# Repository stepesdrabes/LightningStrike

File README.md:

# LightningStrike

Music-driven lighting for a room, with a 3D preview and matching output to real fixtures.
The room has a 671-pixel ceiling frame and a one-pixel Bounce Lamp. Local audio analysis
finds the musical grid; a deterministic engine composes the show. An evening file scripts a
whole night around it: songs, pauses, light moments, transitions and custom effects.

The preview and hardware use the same renderer and encoded pixels. Hardware output runs
in Node over DDP or sACN; the browser supplies the audio playback position.

## Use it

- Search YouTube Music, paste a supported URL, or paste a local audio path.
- Queue tracks, reorder them, or let radio keep the queue supplied.
- Watch the room preview, inspect the arrangement, and configure hardware in the app.
- Use Lounge for ambient lighting over music. When playback stops, the room fades into
  ambient scenes; stale browser sync also lets the hardware return to ambient.
- Open an evening from the right-hand rail, rehearse it, then run the night from there.
- Share the queue's QR code so guests can add tracks from their phones and withdraw their
  own unplayed additions. Queue management, authoring and hardware controls stay with the host.
- Click the LightningStrike mark (⌘,) for Settings: the analysis model and where it runs, the
  browser whose YouTube sign-in downloads use, radio and rest, the library and model folders,
  and the versions of the tools the app relies on.
- Watch Striker 2.0 at the top of the right rail. While a song plays, the view replays what the
  network heard and answered for it, locked to the music; while one prepares, each 90-second
  chunk's input goes in, the stages light in the order data passes them, each for its share of
  the arithmetic, and the outputs come back. The stages are read from the installed graph.

If YouTube refuses downloads on your network (some addresses get every signed-out request
refused while a signed-in browser still plays), choose that browser under Settings, YouTube.
Downloads then carry its YouTube cookies, read fresh each time by yt-dlp; no other site sees
them. macOS asks once for access to the browser's cookie key.

Space toggles playback; arrows seek, with Shift for larger jumps. Cmd/Ctrl-K opens search,
`[` and `]` toggle the side panels, and `L` toggles Lounge.

## Evenings

An evening is a TypeScript file whose default export is `evening(...)` from
`lightningstrike`; keep them in `evenings/`, where `npm run check` type-checks them.
[evenings/light-before-thunder.ts](evenings/light-before-thunder.ts) is a full example.

- `block` plays named songs and `fill` slots chosen by genre, heat, tempo and length;
  `pause` is silence or calm music under a look; `hold` waits for Go; `moment` is a silent
  light moment on its own clock; `narration` plays your own audio under a timeline. Timeline
  steps change looks and sections, fire hits, and place kicks off the grid, like a racing heart.
- A block's `palette` tints its songs toward the chapter's colours without changing the light
  they deliver, and a look laid over songs still rises and falls with their sections: the
  evening sets the colour, each song keeps its intensity.
- `enter` sets how the room hands over: a sting in a gap, a dissolve or a cut, a hit on the
  first downbeat, or an audio crossfade. `at` and `notBefore` anchor segments to the clock;
  fills with a target length stretch or shrink to meet them.
- `effect({ create(g) })` is your own effect, run through the same sandbox and gate as built-in
  ones. Only the effect vocabulary and its own locals exist inside `create`. `look` stacks
  effects with a palette, intensity, motion and `floor`, the house light under them.

The loader runs the file in a worker with a time and memory limit; it may import only
`lightningstrike` and its own relative modules. The worker contains mistakes, not hostile code:
open only evening files you trust. Findings point at file lines. **Prepare** fetches and
analyses the songs the evening names, **Rehearse** plays it exactly as the night, hardware
included, and can be moved to any moment, and **Start** sets the current queue aside until the
evening ends. While it runs, segments are queue rows: skip a segment either way, hold after
the current one, or bail out and keep the music. Guests' requests wait for the blocks that take
them; a song you play now plays straight away and the evening carries on after it. After a
restart the evening comes back where it was, paused.

## Run locally

Use Node 22+ and put `ffmpeg`, `ffprobe` and `yt-dlp` on PATH.

```sh
npm install
npm run dev
```

Open [localhost:5180](http://localhost:5180). The development server also listens on the
LAN for guest access. The app is the product interface; there is no separate playback CLI.

## Build and check

Run commands from the repository root:

```sh
npm test                            # Vitest
npm run check                       # packages, web and controller
npm run build                       # production web build
npm run build -w @mv/desktop         # desktop application and installers
npm run dev -w @mv/controller        # lights controller, localhost:5181
npm run build -w @mv/controller      # static controller build
```

Desktop builds require Rust and the platform's Tauri build prerequisites. The build hook
builds the web server and assembles its Node 24.11.0 sidecar automatically, pinned in
`apps/desktop/scripts/bundle-support.js`. To prepare desktop
development separately, run `npm run bundle -w @mv/desktop`, then
`npm run dev -w @mv/desktop`. The desktop app still expects the audio tools on PATH.
The bundled native runtimes require macOS 14 or newer. Build on Apple Silicon for a native
ARM64 application; Striker 2.0 runs locally, on the GPU through Core ML once it passes its check
there, else on the CPU, without Python or an NVIDIA GPU. Copy its model into `models/` first: the
build refuses to bundle without it.

## How it works

Ingest downloads or copies audio, decodes it with ffmpeg, and produces a `TrackAnalysis`:
beats, bars, sections, spectral features and musical events. Striker 2.0 hears the beats and
drums; metadata, lyrics and a genre model refine the result. The engine turns that analysis
into a bar-addressed `Show`; the linter checks the show before playback. AI authors use the
same contracts and effect gate.

The queue is server state, persisted between runs and observed by clients over SSE. Track
preparation is serialized, prioritizing the current track and the next one. The server
renders hardware frames from the show and browser sync instead of receiving pixel streams
from the browser.

## Repository

| Path | Responsibility |
| --- | --- |
| `apps/web` | SvelteKit player, guest queue and server APIs |
| `apps/desktop` | Tauri window and Node server sidecar |
| `apps/controller` | Standalone web controls for the lights' HTTP API |
| `packages/core` | Contracts, grid, colour, effects/sandbox, mixing and byte encoding |
| `packages/analysis` | Audio ingest, Striker 2.0, DSP and enrichment |
| `packages/author-engine` | Deterministic show composition and linting |
| `packages/author-ai` | AI authoring, tools and effect catalog |
| `packages/preview3d` | three.js room preview |
| `packages/transport` | DDP and sACN output |
| `firmware` | Frame, bench fixture and Bounce Lamp firmware |
| `bench` | Measurement, corpus and model-export tools |

Workspace packages are consumed as TypeScript source. `core` has no external runtime
dependencies, so the same renderer runs in the browser and Node. See [CLAUDE.md](CLAUDE.md)
for development conventions and the rules for changing effects or cached contracts.

The [lighting and drum review harnesses](bench/POLISH.md) provide audio-synchronized output
comparisons, isolated-effect probes and corpus checks without replacing saved shows.

## Cache and models

Workspace runs use the repository's `cache/`, independent of the working directory.
`MV_CACHE_DIR` overrides it. Desktop defaults to its application-local cache directory and
also honors `MV_CACHE_DIR`.

The cache holds audio and each track's `.analysis.json`, `.show.json`, `.meta.json` and
`.context.json`, plus queue state, settings and review data. Treat saved shows, track edits
and settings as user data. Cache and downloaded models are gitignored. Each song prepared by
Striker 2.0 also keeps a `.hearing.bin` (1 to 3 MB, gzipped) for the model view: its input
features, its output heads and the real activations of its kept neurons, in bytes. Nothing
composes a show from it.

After analysis or engine updates, queued tracks refresh as they become current or next.
Preparation reuses saved audio, so the original URL or imported file need not remain
available. Current engine arrangements are retained when the refreshed musical layout matches
and the show remains valid; other engine shows regenerate with their saved reroll seed.
AI-authored arrangements are retained when the audio identity still matches.

Workspace analysis reads `models/`, overridden by `MV_MODEL_DIR`. Desktop uses its bundled
model directory. The models are:

- **Striker 2.0** (`striker2.json` beside its graph, `striker2.onnx`), one network that hears
  drum hits with levels, beats, downbeats, bass note onsets and stem activity at 100 fps.
  Preparation runs it in one stage on the 44.1 kHz decode; its beats go through a DBN to the
  grid, and its kick, snare and hat (with cymbals) are the hits the lights follow. The manifest
  records the graph's SHA-256 and the bass filter's taps, and the graph is checked against them
  before a song is prepared. It is copied in by hand: never committed, never downloaded.
- **Striker 2.0 Small** (`striker2-small.json` and `striker2-small.onnx`), a smaller export of
  the same network for slower machines, chosen in the library dialog. Until its files are in
  `models/` the dialog shows it as not installed and cannot choose it.
- **Discogs-EffNet** for genre evidence, downloaded on demand with a pinned digest.

Without a usable Striker 2.0 nothing is prepared: a missing file, a failed check or a failed run
stops the preparation with its reason, on the queue row and in `.preparation.json`, and never
falls back to another analyser. Songs keep the analyses they have meanwhile. An analysis
records the model's manifest name as `striker`; songs another model made, or made before a
model change, are re-analysed when next prepared. `.preparation.json` records stage timings and
the model's name, provider and warnings, or the error.

Where Striker 2.0 runs is the dialog's other Analysis setting (`analysisProvider`): Auto tries
the graphics card first (Core ML on Apple silicon, DirectML on Windows, CUDA on Linux), CPU is
the processor alone. Only a static graph goes to a graphics provider. Before a provider is used on
a machine it runs the manifest's golden chunks and must match PyTorch: every output within 1e-3,
every decoded event the same, within one frame and 0.01 in level. Otherwise the next one is tried,
ending with the CPU, which is checked too and runs whatever its verdict. Verdicts are kept per
graph, runtime, provider, threads and machine in `cache/striker2-providers.json`, so a pass is
checked once; a provider that fails on a song is marked failed and the song runs again on the CPU.
One session serves a whole preparation run (the ingest worker stays between songs) and closes
after 90 idle seconds. Changing the provider leaves analyses current.

Drum listening is available from the Judge panel. It plays the full song with optional kick
and snare clicks, loops a chosen passage, and keeps missed-hit and timing notes separately
from the show. Click empty space in either drum lane to mark a missed hit; save notes for
later comparison. Drafts remain in the browser if the page reloads.

Discogs-EffNet weights carry CC BY-NC-SA terms; preserve their upstream license. Striker 2.0's
weights, Small's included, are for personal use only, because its training data and teacher are
non-commercial ([models/striker2.NOTICE](models/striker2.NOTICE)). Desktop builds bundle them,
so never distribute a build that contains them.

The authoring API (`/api/author`) uses the Claude Agent SDK with local Claude authentication,
or DeepSeek through `DEEPSEEK_API_KEY` or a key saved in `settings.json`. The app no longer
opens it; shows it designed earlier keep playing.

## Hardware

DDP over UDP port 4048 is the default output; sACN is also available. The Bounce Lamp uses
its own one-pixel stream. Gamma is applied at the host's byte-encoding boundary, so receivers
must preserve those values without applying gamma again. Frames to a board that says it can
take them go out packed, losslessly, so The Frame arrives in one datagram instead of two.

See [firmware/FIRMWARE.md](firmware/FIRMWARE.md) for boards, wiring, the standalone lighting
state machine, HTTP controls, calibration and flashing. The frame uses three SK6812 RGBWW
data lines; shows use RGB while standalone lighting can use the warm-white emitters.

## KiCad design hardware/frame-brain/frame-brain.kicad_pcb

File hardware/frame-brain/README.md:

# The Frame brain board

The soldered replacement for the perfboard in `docs/frame-wiring.md` step 11: a 80 x 68 mm
two-layer carrier that holds the Pico W on headers, the SN74HCT125N behind it, and screw
terminals for power in and four data pairs out. Everything else in the S-BOX (strip fusing,
power injection, the ground bus) stays on WAGOs exactly as the wiring doc describes; only
logic power and data live here.

## What it assumes

- **5 V comes straight from the salvaged PC supply.** There is no 12 V and no buck on this
  board. The wiring doc's LRS-350-12 plus buck arrangement predates this decision.
- Strip current never flows through this board or its ground.
- Lines A/B/C are GP2/GP3/GP4, matching `firmware/node/src/fixture/frame.rs`. Line D is the
  fourth buffer wired to GP5 and its own terminal as a spare, same philosophy as fuse 4: a
  dead line or a split reel means re-terminating a pair, not ordering a new board. Using it
  needs a fourth line added in the firmware.

## Terminals

| Block | Carries | Pins |
|---|---|---|
| J1 `5 V in` | supply | + left, - right, marked on silk |
| J2 `A north+east` | data pair, reel 1 | signal left, pair ground right |
| J3 `B south+west` | data pair, reel 2 | signal left, pair ground right |
| J4 `C beam` | data pair, beam | signal left, pair ground right |
| J5 `D spare` | data pair, unused | signal left, pair ground right |

One twisted pair per line, each with its own ground, as in the wiring doc.

## Protection, and why each part is there

- **F1, 1 A polyfuse.** The PC supply can source tens of amps; the fuse is for the feed wire.
- **D2 across the input.** A reversed supply trips F1 instead of killing anything.
- **D1, 1N5817 into VSYS.** A laptop on the Pico's USB cannot back-feed the 5 V rail. The
  Pico sees about 4.7 V, well inside its 1.8 to 5.5 V VSYS range.
- **C1, 1000 uF.** The WiFi transmit bursts land at the end of a long 5 V feed.
- **C2, 100 nF** tight against the shifter's pin 14.
- **SW1** pulls RUN low: hold BOOTSEL on the Pico and tap it to reach the bootloader without
  touching the supply.
- **D3** says the 5 V rail is up, which is the first thing to check when a line goes dark.

## Bill of materials

| Ref | Part | Note |
|---|---|---|
| J1 to J5 | Phoenix MKDS 1,5/2-5,08 | 5.08 mm screw block; KF301-5.08 clones fit the same footprint |
| U1 | Raspberry Pi Pico W | owned; add 2x 20-pin female header, 2.54 mm |
| U2 | SN74HCT125N | owned; add a DIP-14 socket, it is the replaceable part |
| F1 | Bourns MF-RHT100 | radial polyfuse, 1 A hold |
| D1, D2 | 1N5817 | DO-41 Schottky |
| D3 | LED 3 mm green | |
| R1 to R4 | 330 R axial | owned |
| R5 | 1k axial | |
| C1 | 1000 uF 25 V radial | owned, 10 mm can, 5 mm pitch |
| C2 | 100 nF ceramic | owned, 5 mm pitch |
| SW1 | 6 x 6 mm tactile | |
| H1 to H4 | M3 screw + standoff | mounts to the S-BOX plate |

## Ordering

`fab/frame-brain-revA-gerbers.zip` uploads as is to PCBWay, JLCPCB or Aisler: 2 layer,
1.6 mm, any finish. The design uses 0.5 mm tracks and 0.25 mm clearances, far inside every
fab's default capability, so the cheapest option is fine.

## Assembly

Solder flat to tall: R1 to R5, D1 and D2 (band toward the top edge, marked on silk), the
DIP socket, F1, C2, D3, SW1, the two header strips, C1 (stripe to the right, minus), then
the terminal blocks. Leave the chip and the Pico out.

Power on and check: LED lit, 5.0 V across C1, 5 V on socket pin 14 to pin 7. Power off,
seat the chip (notch toward pin 1 dot) and the Pico (USB toward the board edge), then carry
on with `docs/frame-wiring.md` part 4.

## Regenerating the design

`tools/gen_sch.py` writes the schematic and the project symbol library;
`tools/gen_pcb.py`, run with KiCad's bundled python, writes the routed board;
`tools/check_net.py` proves the extracted netlist matches the intended pin map. Editing the
files in KiCad directly is fine, but rerunning a generator overwrites its output.

ERC runs clean with one deliberate override in the project file: `pin_not_driven` is
ignored, because the only net that trips it is RUN, which the Pico drives through an
internal pull-up that ERC cannot see.

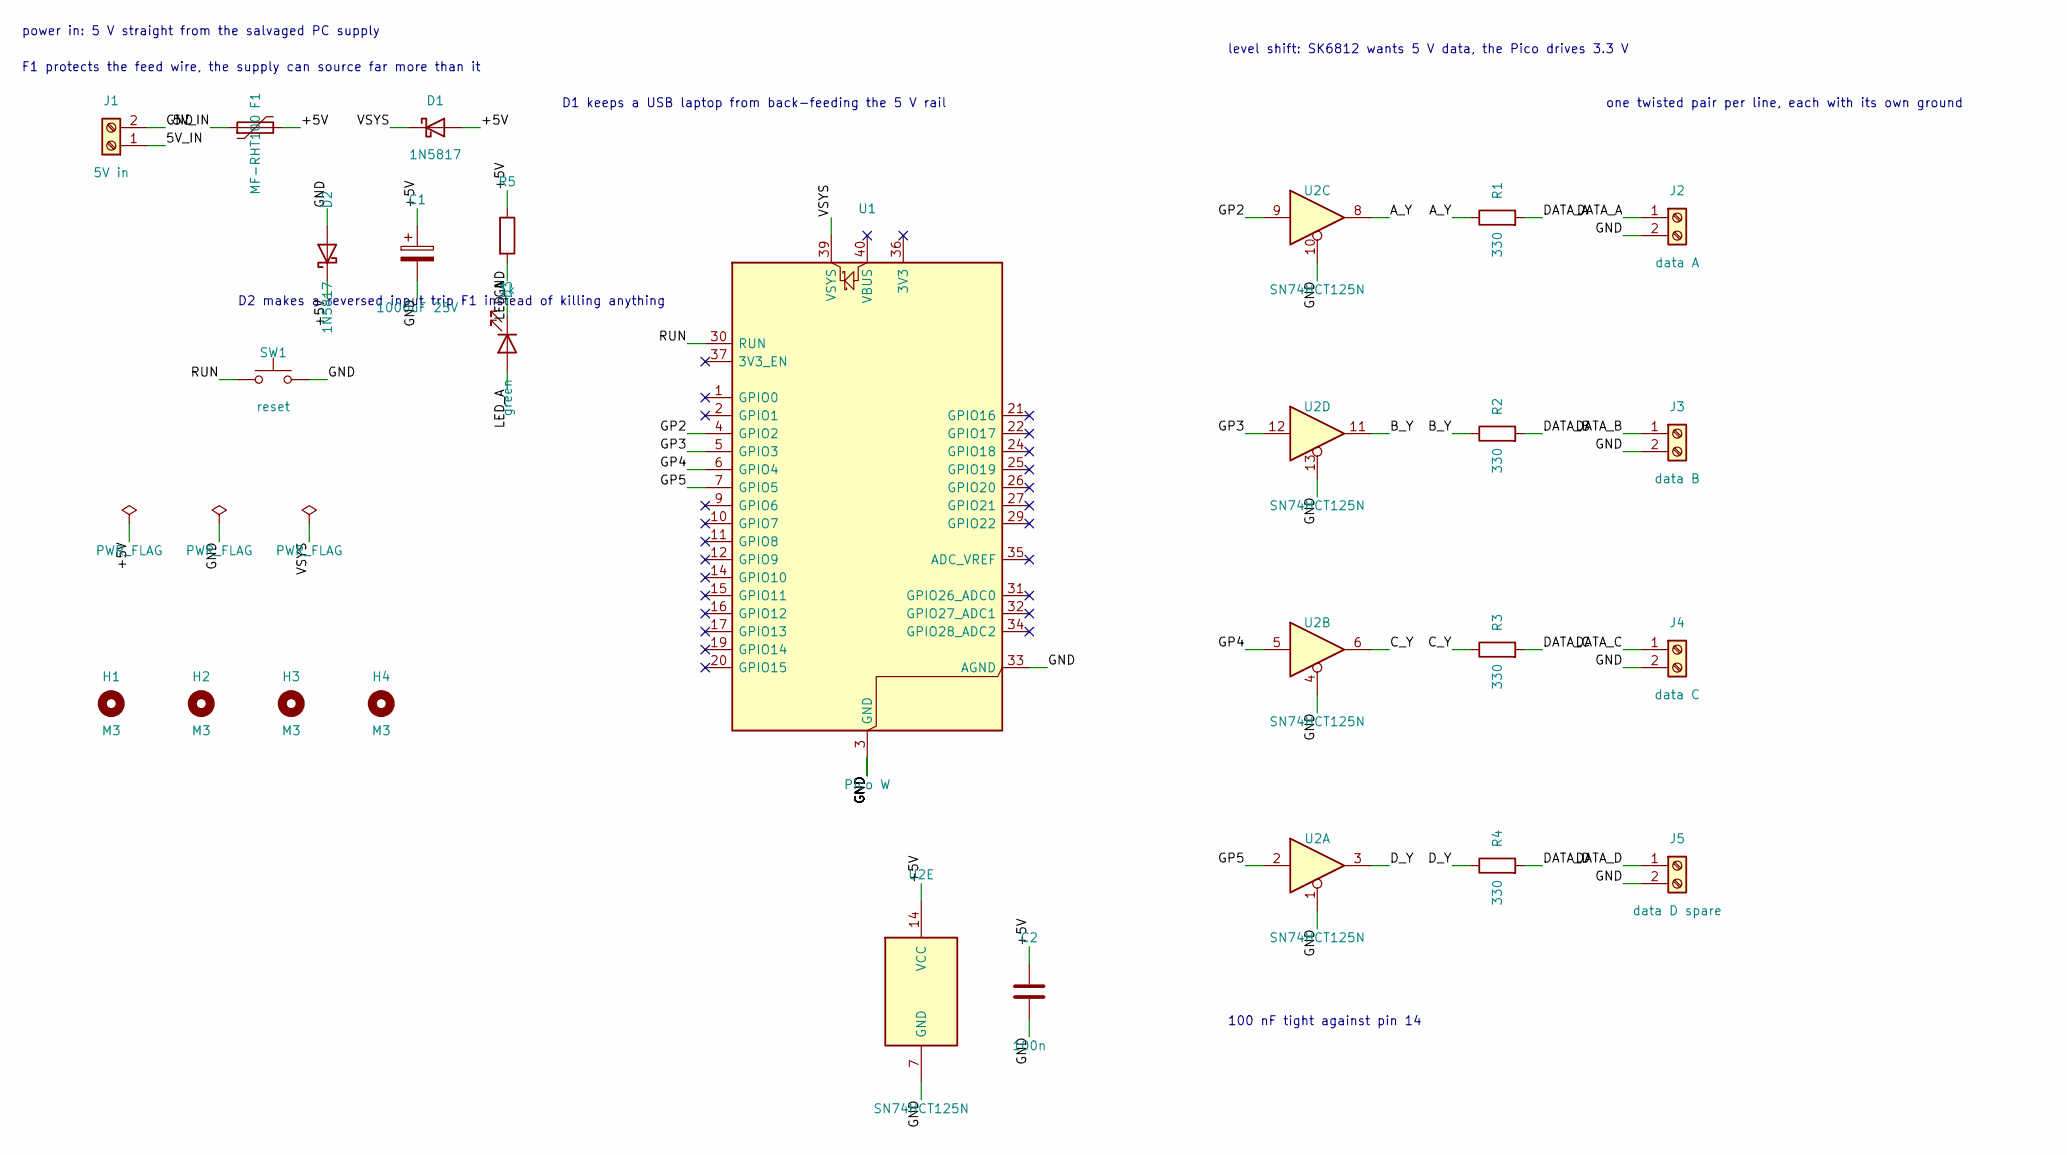
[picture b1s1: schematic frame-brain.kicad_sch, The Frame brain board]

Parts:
C1: 1000uF 25V; CP_Radial_D10.0mm_P5.00mm
C2: 100n; C_Disc_D5.0mm_W2.5mm_P5.00mm
D1, D2: 1N5817; D_DO-41_SOD81_P10.16mm_Horizontal
D3: green; LED_D3.0mm
F1: MF-RHT100; Fuse_Bourns_MF-RHT100
H1, H2, H3, H4: M3; MountingHole_3.2mm_M3
J1: 5V in; TerminalBlock_Phoenix_MKDS-1,5-2-5.08_1x02_P5.08mm_Horizont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
J2: data A; TerminalBlock_Phoenix_MKDS-1,5-2-5.08_1x02_P5.08mm_Horizont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
J3: data B; TerminalBlock_Phoenix_MKDS-1,5-2-5.08_1x02_P5.08mm_Horizont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
J4: data C; TerminalBlock_Phoenix_MKDS-1,5-2-5.08_1x02_P5.08mm_Horizont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
J5: data D spare; TerminalBlock_Phoenix_MKDS-1,5-2-5.08_1x02_P5.08mm_Horizont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
R1, R2, R3, R4: 330; R_Axial_DIN0207_L6.3mm_D2.5mm_P10.16mm_Horizontal
R5: 1k; R_Axial_DIN0207_L6.3mm_D2.5mm_P10.16mm_Horizontal
SW1: reset; SW_PUSH_6mm
U1: Pico W; RaspberryPi_Pico_Common_THT
U2: SN74HCT125N; DIP-14_W7.62mm_Socket

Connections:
/5V_IN: F1.1, J1.1
/+5V: C1.1, C2.1, D1.2 (A), D2.1 (K), F1.2, R5.1, U2.14 (VCC)
/A_Y: R1.1, U2.8
/B_Y: R2.1, U2.11
/C_Y: R3.1, U2.6
/DATA_A: J2.1, R1.2
/DATA_B: J3.1, R2.2
/DATA_C: J4.1, R3.2
/DATA_D: J5.1, R4.2
/D_Y: R4.1, U2.3
/GP2: U1.4 (GPIO2), U2.9
/GP3: U1.5 (GPIO3), U2.12
/GP4: U1.6 (GPIO4), U2.5
/GP5: U1.7 (GPIO5), U2.2
/LED_A: D3.2 (A), R5.2
/RUN: SW1.1, U1.30 (RUN)
/VSYS: D1.1 (K), U1.39 (VSYS)
GND: C1.2, C2.2, D2.2 (A), D3.1 (K), J1.2, J2.2, J3.2, J4.2, J5.2, SW1.2, U1.3 (GND), U1.8 (GND), U1.13 (GND), U1.18 (GND), U1.23 (GND), U1.28 (GND), U1.33 (AGND), U1.38 (GND), U2.1, U2.4, U2.7 (GND), U2.10, U2.13

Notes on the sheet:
power in: 5 V straight from the salvaged PC supply
F1 protects the feed wire, the supply can source far more than it
D1 keeps a USB laptop from back-feeding the 5 V rail
D2 makes a reversed input trip F1 instead of killing anything
level shift: SK6812 wants 5 V data, the Pico drives 3.3 V
one twisted pair per line, each with its own ground
100 nF tight against pin 14

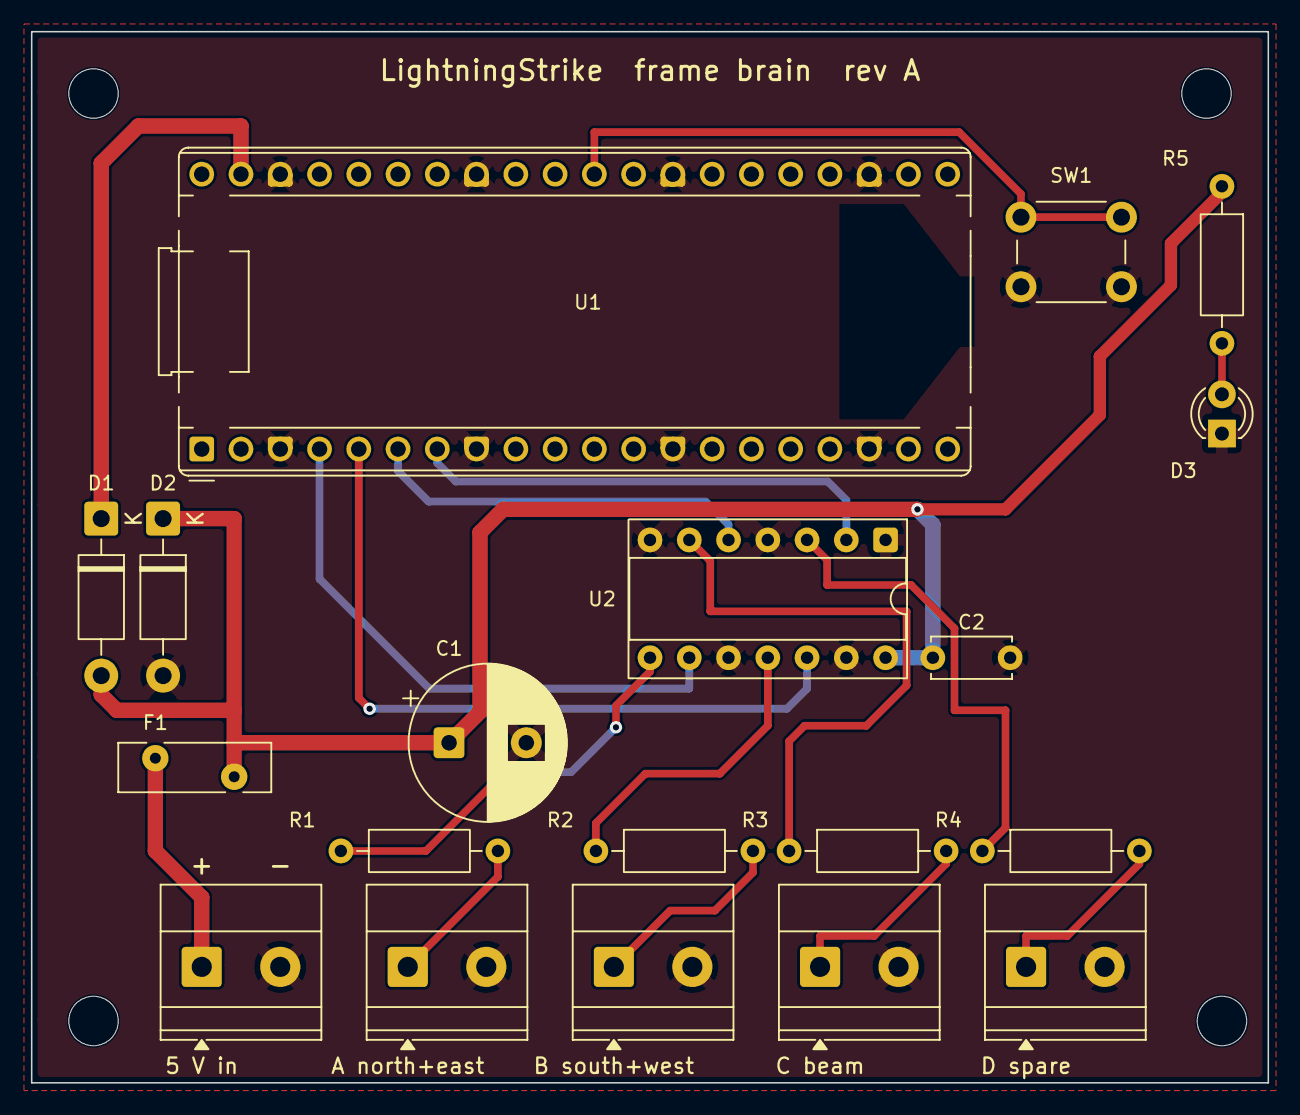
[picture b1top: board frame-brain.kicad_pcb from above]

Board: 2 copper layers, 80.0 x 68.0 mm, 23 parts (0 on the bottom side), 18 nets.
